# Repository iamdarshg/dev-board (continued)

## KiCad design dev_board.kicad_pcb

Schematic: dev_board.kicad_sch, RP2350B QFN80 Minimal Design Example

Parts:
C3: 15p; C_0402_1005Metric; not fitted
C4: 15p; C_0402_1005Metric
C6, C7: 4.7u; C_0402_1005Metric_small_pads
C8, C11, C12, C13, C14, C15, C16, C17, C18, C20, C21, C22, C23, C24, C26, C27, C33, C38, C41, C42, C43, C44, C45, C49, C50, C51, C52, C54, C55, C56, C57, C59, C61, C63, C66, C67, C75, C77, C82, C85, C86, C87, C88, C90, C92, C93, C94: 100n; C_0402_1005Metric
C9, C10: 4.7u; C_0402_1005Metric
C19: 10u; C_0805_2012Metric
C25, C28, C30, C31, C34, C35, C46, C53, C58, C62, C68, C70, C72, C74, C76, C83, C84: 10u; C_0402_1005Metric
C29, C32, C36, C37, C60: 1u; C_0402_1005Metric
C39, C40, C81: 10n; C_0402_1005Metric
C47, C48, C69, C71, C73, C78, C79, C80: 2.2u; C_0402_1005Metric
C89: 1n; C_0402_1005Metric
C91: 22p; C_0402_1005Metric
C95: 47n; C_0402_1005Metric
C96, C97, C98: 100p; C_0402_1005Metric
FL1: 0900PC15A0036; Rohm_MLGA010V020A_LGA-10_2x2mm_P0.45mm_LayoutBorder2x3y
IC1: AD9609BCPZRL7-80; QFN50P500X500X100-33N; Manufacturer_Part_Number AD9609BCPZRL7-80; Mouser Part Number 584-AD9609BCPZR7-80
IC2: ENS161-BLGT_LGA9_T&R_1k5; ENS161BLGTLGA9TR1k5; Manufacturer_Part_Number ENS161-BLGT LGA9 T&R 1k5; Mouser Part Number 135-ENS161BGLTT&R1K5
IC3: ICM-42670-P; ICM42670P; Manufacturer_Part_Number ICM-42670-P; Mouser Part Number 410-ICM-42670-P
IC4: IWRL6432BDBAAMFR; BGA102C50P12X12_645X645X97; Manufacturer_Part_Number IWRL6432BDBAAMFR
IC5, IC10: MP4541GN-Z; SOIC127P600X170-9N; Manufacturer_Part_Number MP4541GN-Z; Mouser Part Number 946-MP4541GN-Z
IC6: THS8136IPHPR; QFP50P900X900X120-49N; Manufacturer_Part_Number THS8136IPHPR; Mouser Part Number 595-THS8136IPHPR
IC7, IC9: TPS40304ADRCR; Manufacturer_Part_Number TPS40304ADRCR; Mouser Part Number 595-TPS40304ADRCR
IC8: XCC1352R1F3RGZR; QFN50P700X700X100-49N-D; Manufacturer_Part_Number XCC1352R1F3RGZR
J2: Conn_02x26_Odd_Even; PinHeader_2x26_P2.54mm_Vertical
J4: SM03B-SRSS-TB; JST_SH_SM03B-SRSS-TB_1x03-1MP_P1.00mm_Horizontal
J5: STM32H7 GPIO/Fabric Breakout A; PinHeader_2x26_P2.54mm_Vertical
J6: STM32H7 GPIO/Fabric Breakout B; PinHeader_2x26_P2.54mm_Vertical
J9: HS/IWRL Fabric Breakout; PinHeader_2x26_P2.54mm_Vertical
J10: RJ45 / 8P8C LED; RJ45_Amphenol_RJMG1BD3B8K1ANR
J11: SMA_RF_LAUNCH; SMA_Amphenol_132134-10_Vertical
J12: RP2350 USB PROGRAM; USB_Micro-B_Amphenol_10103594-0001LF_Horizontal
J13, J14: DNP / not used; USB_Micro-B_Amphenol_10103594-0001LF_Horizontal
J15: IWRL USB PROGRAM; USB_Micro-B_Amphenol_10103594-0001LF_Horizontal
L1: 3.3u; L_pol_2016
L2: 10uH; L_0805_2012Metric
L3: 4.7uH; L_0805_2012Metric
MK1: IM69D120; Infineon_PG-LLGA-5-1
R2, R4, R6, R45, R46, R47, R48: 1k; R_0402_1005Metric
R3, R49, R50: 33; R_0402_1005Metric
R7, R8: 27; R_0402_1005Metric
R9, R10: 4.7k; R_0402_1005Metric
R11, R12, R13, R17, R18, R19, R22, R23, R26, R27, R28, R29: 10k; R_0402_1005Metric
R14: 330k; R_0402_1005Metric
R15, R16: 100k; R_0402_1005Metric
R24: 12.1k; R_0402_1005Metric
R25, R39, R40, R41: 2.2k; R_0402_1005Metric
R30: 0R; R_0402_1005Metric
R31: 3.8k; R_0402_1005Metric
R32, R33, R34, R42, R43, R44: 75; R_0402_1005Metric
R35, R36, R37, R38: 49.9; R_0402_1005Metric
SW1, SW2: SW_Push; SW_Push_1P1T_NO_Vertical_Wuerth_434133025816
TP1, TP2, TP3, TP4, TP5: TestPoint; TestPoint_Pad_3.0x3.0mm
U1: RP2350_80QFN; RP2350-QFN-80-1EP_10x10_P0.4mm_EP3.4x3.4mm_ThermalVias
U2: LPS22HH; ST_HLGA-10_2x2mm_P0.5mm_LayoutBorder3x2y
U3: STM32H750VBTx; LQFP-100_14x14mm_P0.5mm
U4: LAN8742A; VQFN-24-1EP_4x4mm_P0.5mm_EP2.5x2.5mm_ThermalVias
U5: PGA113; TSSOP-10_3x3mm_P0.5mm
U6: MCP6D11T-E/MS; MCP6D11T-E_MSOP-8_3x3mm_P0.65mm
U7: FT232RNL-TUBE; SSOP-28_5.3x10.2mm_P0.65mm
U8: XMSSJJ3G0PA-054; SOT-363_SC-70-6
Y1: ABM8-272-T3; Crystal_SMD_3225-4Pin_3.2x2.5mm
Y2: XRCMD48M000F1P2AR0; Crystal_SMD_2016-4Pin_2.0x1.6mm

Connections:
+3V3: C6.1, C12.1, C13.1, C14.1, C15.1, C16.1, C17.1, C18.1, C19.1, C20.1, C21.1, C22.1, C23.1, C24.1, C25.1, C26.1, C27.1, C28.1, C34.1, C35.1, C41.1, C42.1, C43.1, C44.1, C45.1, C46.1, C50.1, C51.1, C52.1, C62.1, C63.1, C80.1, C81.1, C82.1, C83.1, C84.1, C85.1, C86.1, C88.2, FL1.1 (ANT_2G4), IC2.4 (VDD), IC2.5 (VDDIO), IC3.5 (VDDIO), IC3.7 (FSYNC), IC3.8 (VDD), IC3.12 (AP_CS), IC6.40 (AVDD_2), IC6.44 (AVDD), IC8.13 (VDDS2), IC8.22 (VDDS3), IC8.34 (VDDS_DCDC), IC8.44 (VDDS), J2.2, J9.18, J9.40, J9.44, J9.52, L2.1, L3.2, MK1.5 (GND), R3.1, R9.1, R10.1, R13.1, R14.1, R17.2, R23.2, R25.2, R26.2, R28.2, R39.2, R40.2, R41.2, U1.5 (IOVDD), U1.15 (IOVDD), U1.24 (IOVDD), U1.29 (IOVDD), U1.41 (IOVDD), U1.50 (IOVDD), U1.59 (ADC_AVDD), U1.60 (IOVDD), U1.64 (VREG_VIN), U1.68 (USB_OTP_VDD), U1.69 (QSPI_IOVDD), U1.76 (IOVDD), U2.1 (Vdd_IO), U2.6 (~CS), U2.10 (VDD), U3.6 (VBAT), U3.11 (VDD), U3.20 (VREF+), U3.21 (VDDA), U3.27 (VDD), U3.50 (VDD), U3.75 (VDD), U3.100 (VDD), U4.1 (VDD2A), U4.9 (VDDIO), U4.19 (VDD1A), U5.1 (AV_{DD}), U5.10 (DV_{DD}), U6.3 (VDD), U8.3 (PORT2), U8.4 (VDD)
/ADC_AVDD_1V8: C55.1, C56.1, C57.1, C58.1, IC1.3 (AVDD_2), IC1.24 (AVDD_4), IC1.29 (AVDD_3), IC1.32 (AVDD)
/ADC_CLK_N: IC1.2 (CLK-), J5.18, U3.45 (PE15)
/ADC_CLK_P: IC1.1 (CLK+), J5.17, U3.44 (PE14)
/ADC_CSB: IC1.4 (CSB), J5.14, U3.41 (PE11)
/ADC_D0: IC1.11 ((LSB)D0), J5.3, U3.97 (PE0)
/ADC_D1: IC1.12 (D1), J5.4, U3.98 (PE1)
/ADC_D2: IC1.14 (D2), J5.5, U3.1 (PE2)
/ADC_D3: IC1.15 (D3), J5.6, U3.2 (PE3)
/ADC_D4: IC1.16 (D4), J5.7, U3.3 (PE4)
/ADC_D5: IC1.17 (D5), J5.8, U3.4 (PE5)
/ADC_D6: IC1.18 (D6), J5.9, U3.5 (PE6)
/ADC_D7: IC1.19 (D7), J5.10, U3.37 (PE7)
/ADC_D8: IC1.20 (D8), J5.11, U3.38 (PE8)
/ADC_D9: IC1.21 (D9(MSB)), J5.12, U3.39 (PE9)
/ADC_DCO: IC1.22 (DCO), J5.13, U3.40 (PE10)
/ADC_DRVDD: C59.1, IC1.13 (DRVD0)
/ADC_MODE_OR: IC1.23 (MODE/OR)
/ADC_RBIAS: IC1.28 (RBIAS), R29.1
/ADC_SCLK: IC1.5 (SCLK/DFS), J5.15, U3.42 (PE12)
/ADC_SDIO: IC1.6 (SDIO/PDWN), J5.16, U3.43 (PE13)
/ADC_SENSE: IC1.26 (SENSE), R30.1
/ADC_VCM: C61.1, IC1.27 (VCM), R46.1, U5.4 (V_{REF}), U6.2 (VOCM)
/ADC_VIN_N: C91.2, IC1.30 (VIN-), R49.2
/ADC_VIN_P: C91.1, IC1.31 (VIN+), R50.2
/ADC_VREF: C60.1, IC1.25 (VREF), R30.2
/CC_DCDC_SW: IC8.33 (DCDC_SW), L2.2
/CC_DCOUPL: C29.1, IC8.23 (DCOUPL)
/CC_DIO_3: IC8.8 (DIO_3), J6.31
/CC_DIO_4: IC8.9 (DIO_4), J6.32
/CC_DIO_5: IC8.10 (DIO_5), J6.33
/CC_DIO_7: IC3.9 (INT2), IC8.12 (DIO_7), J2.39, J6.35, U1.36 (GPIO28)
/CC_DIO_8: IC8.14 (DIO_8), J2.37, J6.36, U1.37 (GPIO29)
/CC_DIO_9: IC8.15 (DIO_9), J2.35, J6.37, U1.38 (GPIO30)
/CC_DIO_10: IC8.16 (DIO_10), J2.33, J6.38, U1.39 (GPIO31)
/CC_DIO_11: IC8.17 (DIO_11), J6.39
/CC_DIO_12: IC8.18 (DIO_12), J6.40
/CC_DIO_13: IC8.19 (DIO_13), J6.41
/CC_DIO_14: IC8.20 (DIO_14), J6.42
/CC_DIO_15: IC8.21 (DIO_15), J6.43
/CC_DIO_16: IC8.26 (DIO_16), J6.44
/CC_DIO_17: IC8.27 (DIO_17), J9.39
/CC_DIO_18: IC8.28 (DIO_18), J6.46
/CC_DIO_19: IC8.29 (DIO_19), J9.41
/CC_DIO_20: IC8.30 (DIO_20), J6.48
/CC_DIO_21: IC8.31 (DIO_21), J9.43
/CC_DIO_22: IC8.32 (DIO_22), J6.50
/CC_DIO_23: IC8.36 (DIO_23), J9.45
/CC_DIO_24: IC8.37 (DIO_24), J6.52
/CC_DIO_25: IC8.38 (DIO_25), J9.47
/CC_DIO_26: IC8.39 (DIO_26), J6.51
/CC_DIO_27: IC8.40 (DIO_27), J9.49
/CC_DIO_28: IC8.41 (DIO_28), J6.49
/CC_DIO_29: IC8.42 (DIO_29), J9.51
/CC_DIO_30: C97.2, FL1.4 (ANT_SUBG), IC8.43 (DIO_30), J6.47, U8.6 (CTL)
/CC_PROG_USB_D+: J14.3 (D+)
/CC_PROG_USB_D-: J14.2 (D-)
/CC_PROG_USB_VBUS: J14.4 (ID)
/CC_RESET_N: IC8.35 (RESET_N), J9.46, R13.2
/CC_RF_N_2G4: FL1.8 (RF_N_2G4), IC8.2 (RF_N_2_4GHZ)
/CC_RF_N_SUBG: FL1.6 (RF_N_SUBG), IC8.4 (RF_N_SUB_1GHZ)
/CC_RF_P_2G4: C98.2, FL1.9 (RF_P_2G4), IC8.1 (RF_P_2_4GHZ)
/CC_RF_P_SUBG: FL1.7 (RF_P_SUBG), IC8.3 (RF_P_SUB_1GHZ)
/CC_TCKC: IC8.25 (JTAG_TCKC), J6.45
/CC_TMSC: IC8.24 (JTAG_TMSC), J9.50
/CC_VDDR: C30.1, IC8.45 (VDDR), IC8.48 (VDDR_RF)
/CC_X32K_Q1: IC8.6 (X32K_Q1)
/CC_X32K_Q2: IC8.7 (X32K_Q2)
/CC_X48M_N: IC8.46 (X48M_N), Y2.3
/CC_X48M_P: IC8.47 (X48M_P), Y2.1
/DAC_B0: IC6.10 (B0), J5.19, U3.81 (PD0)
/DAC_B1: IC6.9 (B1), J5.20, U3.82 (PD1)
/DAC_B2: IC6.8 (B2), J5.21, U3.83 (PD2)
/DAC_B3: IC6.7 (B3), J5.22, U3.84 (PD3)
/DAC_B4: IC6.6 (B4), J5.23, U3.85 (PD4)
/DAC_B5: IC6.5 (B5), J5.24, U3.86 (PD5)
/DAC_B6: IC6.4 (B6), J5.25, U3.87 (PD6)
/DAC_B7: IC6.3 (B7), J5.26, U3.88 (PD7)
/DAC_B8: IC6.2 (B8), J5.27, U3.55 (PD8)
/DAC_B9: IC6.1 (B9), J5.28, U3.56 (PD9)
/DAC_BLANK_N: IC6.23 (~BLANK), J6.24, R40.1, U3.66 (PC9)
/DAC_CLK: IC6.26 (CLK), J6.21, R39.1, U3.63 (PC6)
/DAC_COMP: C66.1, IC6.39 (COMP)
/DAC_FSADJ: IC6.38 (FSADJ), R31.1
/DAC_G0: IC6.36 (G0), J5.29, U3.57 (PD10)
/DAC_G1: IC6.35 (G1), J5.30, U3.58 (PD11)
/DAC_G2: IC6.34 (G2), J5.31, U3.59 (PD12)
/DAC_G3: IC6.33 (G3), J5.32, U3.60 (PD13)
/DAC_G4: IC6.32 (G4), J5.33, U3.61 (PD14)
/DAC_G5: IC6.31 (G5), J5.34, U3.62 (PD15)
/DAC_G6: IC6.30 (G6), J5.51, U3.34 (PB0)
/DAC_G7: IC6.29 (G7), J5.52, U3.35 (PB1)
/DAC_G8: IC6.28 (G8), J6.1, U3.36 (PB2)
/DAC_G9: IC6.27 (G9), J6.2, U3.89 (PB3)
/DAC_M1: IC6.47 (M1), J6.25, U3.78 (PC10)
/DAC_M2: IC6.48 (M2), J6.26, U3.79 (PC11)
/DAC_R0: IC6.13 (R0), J6.3, U3.90 (PB4)
/DAC_R1: IC6.14 (R1), J6.4, U3.91 (PB5)
/DAC_R2: IC6.15 (R2), J6.7, U3.95 (PB8)
/DAC_R3: IC6.16 (R3), J6.8, U3.96 (PB9)
/DAC_R4: IC6.17 (R4), J5.2, U3.13 (PH1)
/DAC_R5: IC6.18 (R5), J6.13, U3.53 (PB14)
/DAC_R6: IC6.19 (R6), J6.14, U3.54 (PB15)
/DAC_R7: IC6.20 (R7), J6.15, U3.15 (PC0)
/DAC_R8: IC6.21 (R8), J6.17, U3.17 (PC2_C)
/DAC_R9: IC6.22 (R9), J6.10, U3.47 (PB11)
/DAC_SYNC_N: IC6.24 (~SYNC), J6.23, R41.1, U3.65 (PC8)
/DAC_SYNC_T: IC6.25 (SYNC-T), J6.22, U3.64 (PC7)
/DAC_VREF: C67.1, IC6.37 (VREF)
/ENS_ADDR: IC2.3 (MISO_/_ADDR), R11.1
/ETH_CRS_DV: J5.42, U3.31 (PA7), U4.11 (CRS_DV/MODE2)
/ETH_CT: C87.1, R35.2, R36.2, R37.2, R38.2
/ETH_CT1: J10.5 (CT2)
/ETH_CT2: J10.4 (CT1)
/ETH_MDC: J6.16, U3.16 (PC1), U4.13 (MDC)
/ETH_MDIO: J5.37, R25.1, U3.24 (PA2), U4.12 (MDIO)
/ETH_REFCLK_INT: J5.36, U3.23 (PA1), U4.14 (~INT/REFCLKO)
/ETH_RST_N: R26.1, U4.15 (~RST)
/ETH_RXD0: J6.19, U3.32 (PC4), U4.8 (RXD0/MODE0)
/ETH_RXD1: J6.20, U3.33 (PC5), U4.7 (RXD1/MODE1)
/ETH_RXER: U4.10 (RXER/PHYAD0)
/ETH_RX_N: J10.6 (RD-), R38.1, U4.22 (RXN)
/ETH_RX_P: J10.3 (RD+), R37.1, U4.23 (RXP)
/ETH_TXD0: J6.11, U3.51 (PB12), U4.17 (TXD0)
/ETH_TXD1: J6.12, U3.52 (PB13), U4.18 (TXD1)
/ETH_TXEN: J6.9, U3.46 (PB10), U4.16 (TXEN)
/ETH_TX_N: J10.2 (TD-), R36.1, U4.20 (TXN)
/ETH_TX_P: J10.1 (TD+), R35.1, U4.21 (TXP)
/GPIO0: J2.4, U1.77 (GPIO0)
/GPIO1: J2.6, U1.78 (GPIO1)
/GPIO2: J2.8, MK1.3 (CLOCK), U1.79 (GPIO2)
/GPIO3: J2.10, MK1.4 (SELECT), U1.80 (GPIO3)
/GPIO4: J2.12, MK1.1 (DATA), U1.1 (GPIO4)
/GPIO5: J2.14, U1.2 (GPIO5)
/GPIO7: IC3.4 (INT1_/_INT), J2.18, U1.4 (GPIO7)
/GPIO8: J2.20, U1.6 (GPIO8)
/GPIO9: J2.22, U1.7 (GPIO9), U2.7 (INT_DRDY)
/GPIO10: J2.24, U1.8 (GPIO10), U5.7 (SCLK)
/GPIO11: J2.26, U1.9 (GPIO11), U5.8 (DIO)
/GPIO12: J2.28, U1.11 (GPIO12), U5.9 (~CS)
/GPIO13: J2.30, U1.12 (GPIO13), U6.7 (~PD)
/GPIO14: J2.32, U1.13 (GPIO14)
/GPIO15: J2.34, U1.14 (GPIO15)
/GPIO16: J2.36, J5.35, J9.1, U1.16 (GPIO16), U3.22 (PA0)
/GPIO17: J2.38, J5.38, J9.2, U1.17 (GPIO17), U3.25 (PA3)
/GPIO18: J2.40, J5.39, J9.3, U1.18 (GPIO18), U3.28 (PA4)
/GPIO19: J2.42, J5.40, J9.4, U1.19 (GPIO19), U3.29 (PA5)
/GPIO20: J2.44, J5.41, J9.5, U1.20 (GPIO20), U3.30 (PA6)
/GPIO21: J2.46, J5.43, J9.6, U1.21 (GPIO21), U3.67 (PA8)
/GPIO22: J2.48, J5.44, J9.7, U1.22 (GPIO22), U3.68 (PA9)
/GPIO23: J2.50, J5.45, J9.8, U1.23 (GPIO23), U3.69 (PA10)
/GPIO24: J2.52, J5.46, J9.9, U1.25 (GPIO24), U3.70 (PA11)
/GPIO25: J2.51, J5.47, J9.10, U1.26 (GPIO25), U3.71 (PA12)
/GPIO26: J2.49, U1.27 (GPIO26)
/GPIO32: IC4.A10 (QSPI_CS), J2.31, J5.50, J9.11, U1.40 (GPIO32), U3.77 (PA15)
/GPIO33: IC4.A11 (QSPI_CLK), J2.29, J6.27, J9.12, U1.42 (GPIO33), U3.80 (PC12)
/GPIO34: IC4.B11 (QSPI[0]), J2.27, J6.28, J9.13, U1.43 (GPIO34), U3.7 (PC13)
/GPIO35: IC4.B8 (QSPI[1]), J2.25, J6.29, J9.14, U1.44 (GPIO35), U3.8 (PC14)
/GPIO36: IC4.B10 (QSPI[2]), J2.23, J6.30, J9.15, U1.45 (GPIO36), U3.9 (PC15)
/GPIO37: IC4.B9 (QSPI[3]), J2.21, J5.1, J9.16, U1.46 (GPIO37)
/GPIO38: J2.19, U1.47 (GPIO38)
/GPIO39: J2.17, U1.48 (GPIO39)
/GPIO40_ADC0: J2.15, U1.49 (GPIO40_ADC0)
/GPIO41_ADC1: J2.13, U1.52 (GPIO41_ADC1)
/GPIO42_ADC2: J2.11, U1.53 (GPIO42_ADC2)
/GPIO43_ADC3: J2.9, U1.54 (GPIO43_ADC3)
/GPIO44_ADC4: J2.7, U1.55 (GPIO44_ADC4)
/GPIO45_ADC5: J2.5, U1.56 (GPIO45_ADC5)
/GPIO46_ADC6: J2.3, U1.57 (GPIO46_ADC6)
/GPIO47_ADC7: J2.1, U1.58 (GPIO47_ADC7)
/IMU_AD0: IC3.1 (AP_SDO_/_AP_AD0)
/IWR_CLKM: IC4.B1 (CLKM)
/IWR_CLKP: IC4.D1 (CLKP)
/IWR_FTDI_3V3OUT: C94.1, U7.17 (3V3OUT)
/IWR_GPADC1: IC4.M6 (GPADC1), J9.36
/IWR_GPADC2: IC4.L6 (GPADC2), J9.37
/IWR_GPIO_2: IC4.H10 (GPIO_2), J9.32
/IWR_GPIO_5: IC4.J10 (GPIO_5), J9.33
/IWR_HOST_CLK_REQ: IC4.M10 (HOST_CLK__REQ), J9.34
/IWR_NERROR: IC4.K11 (NERROR__OUT), J9.31
/IWR_NRST: IC4.L10 (NRESET), J9.26
/IWR_OSC_CLK_OUT: IC4.A7 (OSC_CLK__OUT)
/IWR_PMIC_CLKOUT: IC4.H11 (PMIC__CLKOUT), J9.35
/IWR_PROG_USB_D+: J15.3 (D+), U7.15 (USBD+)
/IWR_PROG_USB_D-: J15.2 (D-), U7.16 (USBD-)
/IWR_RX1: IC4.K1 (RX1)
/IWR_RX2: IC4.H1 (RX2)
/IWR_RX3: IC4.F1 (RX3)
/IWR_SPI_CLK: IC4.D10 (SPIA_CLK), J9.21
/IWR_SPI_CS_N: IC4.D11 (SPIA_CS0__N), J9.22
/IWR_SPI_MISO: IC4.C11 (SPIA_MISO), J9.20
/IWR_SPI_MOSI: IC4.B12 (SPIA_MOSI), J9.19
/IWR_TCK: IC4.C12 (TCK), J9.27
/IWR_TDI: IC4.G11 (TDI), J9.29
/IWR_TDO: IC4.E11 (TDO), J9.30
/IWR_TMS: IC4.E12 (TMS), J9.28
/IWR_TX1: IC4.A3 (TX1)
/IWR_TX2: IC4.A5 (TX2)
/IWR_UART_RTS: IC4.L11 (UARTA_RTS), J9.25
/IWR_UART_RX: IC4.J11 (UARTA_RX), J9.24, U7.1 (TXD)
/IWR_UART_TX: IC4.L12 (UARTA_TX), J9.23, U7.5 (RXD)
/IWR_USB_VBUS: C92.1, J15.1 (VBUS), U7.20 (VCC)
/IWR_VDDA_1V0RF: C72.1, C73.1, IC4.L3 (VDDA_10RF_1), IC4.M3 (VDDA_10RF_2)
/IWR_VDDA_1V2RF: C68.1, C69.1, IC4.L4 (VDDA_12RF_1), IC4.M4 (VDDA_12RF_2)
/IWR_VDDA_1V8: C76.1, C77.1, IC4.F3 (VDDA__18VCO), IC4.J5 (VIN_18PM), IC4.L5 (VDDA_18BB_1), IC4.M5 (VDDA_18BB_2)
/IWR_VDD_1V2: IC4.C9 (VDD_1), IC4.G7 (VDD_2), IC4.G8 (VDD_3), IC4.G9 (VDD_4), IC4.H8 (VDD_5), IC4.K7 (VDD_6)
/IWR_VDD_SRAM: C70.1, C71.1, IC4.M7 (VDD_SRAM)
/IWR_VIO_1V8: C74.1, C75.1, C93.1, IC4.C6 (VIOIN__18CLK), IC4.C8 (VIOIN_18_1), IC4.G12 (VIOIN_1), IC4.K12 (VIOIN_18_2), IC4.L8 (VIOIN_18_3), IC4.M8 (VIOIN_18_4), IC4.M11 (VIOIN_2), U7.4 (VCCIO), U7.19 (~RESET)
/IWR_VOUT_1V4_APLL: C79.1, IC4.G5 (VOUT__14APLL)
/IWR_VOUT_1V4_SYNTH: C78.1, IC4.D3 (VOUT__14SYNTH)
/IWR_VPP: IC4.A8 (VPP)
/LPS_SA0: R12.1, U2.5 (SA0)
/MP_BST: C33.1, IC5.5 (BST), IC10.5 (BST)
/MP_EN: IC5.1 (EN), IC10.1 (EN), R16.2
/MP_FB: IC5.4 (FB), IC10.4 (FB), R14.2, R15.1
/MP_FREQ: IC5.3 (FREQ), IC10.3 (FREQ)
/MP_SW: C33.2, IC5.6 (SW), IC10.6 (SW), L3.1
/MP_VCC: C32.1, IC5.2 (VCC), IC10.2 (VCC)
/PHY_LED1_REGOFF: J10.9 (LED1A), R27.1, U4.3 (LED1/REGOFF)
/PHY_LED2_INTSEL: J10.11 (LED2A), R28.1, U4.2 (LED2/~INTSEL)
/PHY_RBIAS: R24.1, U4.24 (RBIAS)
/PHY_VDDCR: C53.1, C54.1, U4.6 (VDDCR)
/PHY_XTAL1: U4.5 (XTAL1/CLKIN)
/PHY_XTAL2: U4.4 (XTAL2)
/QSPI_SCLK: U1.71 (QSPI_SCLK)
/QSPI_SD0: U1.72 (QSPI_SD0)
/QSPI_SD1: U1.74 (QSPI_SD1)
/QSPI_SD2: U1.73 (QSPI_SD2)
/QSPI_SD3: U1.70 (QSPI_SD3)
/QSPI_SS: R6.1, U1.75 (QSPI_SS)
/RUN: J2.41, SW2.2, U1.35 (RUN)
/SCOPE_AUX_IN: TP2.1, U5.2 (CH1)
/SCOPE_IN: TP1.1, U5.3 (CH0/V_{CAL})
/SENS_I2C_SCL: IC2.2 (SCLK_/_SCL), IC3.13 (AP_SCL_/_AP_SCLK), J6.5, R9.2, U2.2 (SCL), U3.92 (PB6)
/SENS_I2C_SDA: IC2.1 (MOSI_/_SDA), IC3.14 (AP_SDA_/_AP_SDIO_/_AP_SDI), J6.6, R10.2, U2.4 (SDA), U3.93 (PB7)
/STM_NRST: C49.1, R23.1, U3.14 (NRST)
/STM_PC3_C: J6.18, U3.18 (PC3_C)
/STM_SWCLK: J5.49, U3.76 (PA14)
/STM_SWDIO: J5.48, U3.72 (PA13)
/STM_USB_FS_DM: J13.2 (D-)
/STM_USB_FS_DP: J13.3 (D+)
/STM_USB_VBUS: J13.1 (VBUS)
/STM_VCAP1: C47.1, U3.48 (VCAP)
/STM_VCAP2: C48.1, U3.73 (VCAP)
/STM_VCAP_A: U3.12 (PH0)
/TPS_BOOT: C38.1, IC7.6 (BOOT), IC9.6 (BOOT)
/TPS_BP: C37.1, IC7.10 (BP), IC9.10 (BP)
/TPS_COMP: C40.1, IC7.4 (COMP), IC9.4 (COMP), R22.1
/TPS_ENSS: C39.1, IC7.2 (EN/SS), IC9.2 (EN/SS)
/TPS_FB: IC7.5 (FB), IC9.5 (FB), R18.2, R19.1, R22.2
/TPS_HDRV: IC7.7 (HDRV), IC9.7 (HDRV)
/TPS_LDRV_OC: IC7.9 (LDRV/_OC), IC9.9 (LDRV/_OC)
/TPS_PGOOD: IC7.3 (PGOOD), IC9.3 (PGOOD), R17.1
/TPS_SW: C38.2, IC7.8 (SW), IC9.8 (SW)
/USB_D+: J12.3 (D+), R7.1
/USB_D-: J12.2 (D-), R8.1
/VGA_B: IC6.45 (AB), R34.1, R44.1, TP4.1
/VGA_G: IC6.41 (AG), R33.1, R43.1, TP5.1
/VGA_MON: R42.2, R43.2, R44.2
/VGA_R: IC6.43 (AR), R32.1, R42.1, TP3.1
/VIN_RAW: C31.1, C36.1, IC5.8 (VIN), IC7.1 (VDD), IC9.1 (VDD), IC10.8 (VIN), J12.1 (VBUS), J14.1 (VBUS), R16.1
/VREG_AVDD: C9.1, R3.2, U1.61 (VREG_AVDD)
/VREG_FB: U1.34 (SWD)
/XIN: C3.1, U1.30 (XIN), Y1.1
/XOUT: R2.1, U1.31 (XOUT)
/~USB_BOOT: R6.2, SW1.2
GND: C3.2, C4.2, C6.2, C7.2, C8.2, C9.2, C10.2, C11.2, C12.2, C13.2, C14.2, C15.2, C16.2, C17.2, C18.2, C19.2, C20.2, C21.2, C22.2, C23.2, C24.2, C25.2, C26.2, C27.2, C28.2, C29.2, C30.2, C31.2, C32.2, C34.2, C35.2, C36.2, C37.2, C39.2, C40.2, C41.2, C42.2, C43.2, C44.2, C45.2, C46.2, C47.2, C48.2, C49.2, C50.2, C51.2, C52.2, C53.2, C54.2, C55.2, C56.2, C57.2, C58.2, C59.2, C60.2, C61.2, C62.2, C63.2, C66.2, C67.2, C68.2, C69.2, C70.2, C71.2, C72.2, C73.2, C74.2, C75.2, C76.2, C77.2, C78.2, C79.2, C80.2, C81.2, C82.2, C83.2, C84.2, C85.2, C86.2, C87.2, C88.1, C89.1, C90.1, C92.2, C93.2, C94.2, C98.1, FL1.2 (GND), FL1.3 (GND), FL1.10 (GND), IC1.33 (EPAD), IC2.8 (VSS_1), IC2.9 (VSS_2), IC3.6 (GND), IC4.A1 (VSSA_1), IC4.A2 (VSSA_2), IC4.A4 (VSSA_3), IC4.A6 (VSSA_4), IC4.B2 (VSSA_5), IC4.B3 (VSSA_6), IC4.B4 (VSSA_7), IC4.B5 (VSSA_8), IC4.B6 (VSSA_9), IC4.B7 (VSS_2), IC4.C1 (VSSA_10), IC4.C2 (VSSA_11), IC4.D2 (VSSA_12), IC4.E1 (VSSA_13), IC4.E2 (VSSA_14), IC4.E5 (VSSA_PM), IC4.E6 (VSS_3), IC4.E7 (VSS_4), IC4.E8 (VSS_5), IC4.E9 (VSS_6), IC4.F2 (VSSA_15), IC4.F5 (VSSA_16), IC4.F6 (VSS_7), IC4.F7 (VSS_8), IC4.F8 (VSS_9), IC4.F9 (VSS_10), IC4.G1 (VSSA_17), IC4.G2 (VSSA_18), IC4.H2 (VSSA_19), IC4.H12 (VSS_11), IC4.J1 (VSSA_20), IC4.J2 (VSSA_21), IC4.K2 (VSSA_22), IC4.K9 (VSS_12), IC4.L1 (VSSA_23), IC4.L2 (VSSA_24), IC4.M1 (VSSA_25), IC4.M2 (VSSA_26), IC4.M12 (VSS_13), IC5.7 (GND), IC5.9 (EP), IC6.11 (DVSS), IC6.12 (DVDD), IC6.42 (AVSS_2), IC6.46 (AVSS), IC6.49 (EP), IC7.11 (GND_1), IC7.12 (GND_2), IC7.13 (GND_3), IC7.14 (GND_4), IC7.15 (GND_5), IC8.49 (EP), IC9.11 (GND_1), IC9.12 (GND_2), IC9.13 (GND_3), IC9.14 (GND_4), IC9.15 (GND_5), IC10.7 (GND), IC10.9 (EP), J4.2, J4.MP (MountPin), J9.17, J9.38, J9.42, J9.48, J10.13 (Shield), J11.2 (Ext), J12.5 (GND), J12.6 (Shield), J13.5 (GND), J13.6 (Shield), J14.5 (GND), J14.6 (Shield), J15.5 (GND), J15.6 (Shield), MK1.2 (VDD), R4.2, R11.2, R12.2, R15.2, R19.2, R24.2, R27.2, R29.2, R31.2, R32.2, R33.2, R34.2, SW1.1, U1.62 (VREG_PGND), U1.81 (GND), U2.3 (GND), U2.8 (GND), U2.9 (GND), U3.10 (VSS), U3.19 (VSSA), U3.26 (VSS), U3.49 (VSS), U3.74 (VSS), U3.94 (BOOT0), U3.99 (VSS), U4.25 (VSS), U5.6 (GND), U6.6 (VSS), U7.7 (GND), U7.18 (GND), U7.21 (GND), U7.25 (AGND), U7.26 (TEST), U8.2 (GND), Y1.2, Y1.4, Y2.2, Y2.4
unnamed: C4.1, R2.2, Y1.3
unnamed: C96.1, J11.1 (In)
unnamed: C96.2, U8.5 (RFC)
unnamed: C97.1, U8.1 (PORT1)
unnamed: FL1.5 (RX_TX), IC8.5 (RX_TX)
unnamed: R4.1, SW2.1
unnamed: R8.2, U1.66 (USB_DM)
unnamed: R7.2, U1.67 (USB_DP)
unnamed: R45.1, U5.5 (V_{OUT})
unnamed: R45.2, R48.1, U6.8 (IN+)
unnamed: C89.2, R46.2, R47.1, U6.1 (IN-)
unnamed: C90.2, R47.2, R50.1, U6.4 (OUT+)
unnamed: R48.2, R49.1, U6.5 (OUT-)

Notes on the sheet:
DAC island: PD/PB/PC/PH1 assigned to THS8136 RGB bus/timing; fabric is kept off these pins.
CC1352 island: recommended decoupling, DCDC and crystal nets
Schematic completion notes
Review before layout: RF matching, ADC analog front-end, Ethernet magnetics, and regulator loop values are topology-dependent.
USB programming ports: J12 RP2350 native USB; J13 STM32 DFU optional via R52/R53; J14 CC1352 programmer bridge USB input, DNP in this revision; J15 IWRL USB-UART at 1.8V I/O.
RJ45 Ethernet island: cable connector / MagJack-side breakout for LAN8742A pairs and LEDs.
CC1352: DCOUPL/VDDR/DCDC support is shown; RF balun/matching network should follow the selected reference design.
Extra explicit passives from datasheet application/BOM sections
RP2350 scope control: GPIO10=PGA SCLK, GPIO11=PGA SDIO, GPIO12=PGA CS_N, GPIO13=MCP6D11 PD_N
IOs
ADC island: AD9609 AVDD/DRVDD/VREF/VCM/RBIAS support
12MHz Crystal
ADC and THS8136 analog support below boundary
CC1352 island: DCOUPL/VDDR/DCDC/crystal support
Power
Codex generated recommended support components - cross-boundary data uses labels only
No generated data wire crosses the horizontal user boundary; shared signals use local net labels.
ADC island: PE0-PE15 assigned to AD9609 data/control/clock nets
Electrical net names preserve existing RP2350 GPIO labels; role notes map those GPIOs to HS_Dx/QSPI functions.
STM32H750 and LAN8742A support below boundary
Ethernet island: LAN8742A RBIAS, VDDCR, magnetics termination
Keep exact/application-specific values for PHY RBIAS 12.1k, Ethernet 49.9R, video 75R, DAC FSADJ 3.8k.
Intentional crossings: GPIO16-GPIO25 are RP-to-STM parallel fabric; GPIO32-GPIO37 are shared RP/STM/IWR QSPI.
STM32/LAN8742A: RMII nets are label-connected below the boundary; unused STM32 GPIOs are intentionally left for expansion.
RF SMA launch: stuff after selected CC1352 balun/matching network; keep 50 ohm controlled impedance.
Place 1k FDA gain/feedback resistors tight to MCP6D11 pins; place 33R/22p ADC filter tight to AD9609 VIN pins.
Buck regulator recommended bootstrap, feedback, soft-start and compensation parts
Boot/strap pins are tied by labels and pull resistors; change these only with firmware/boot-mode review.
Island plan: PE=ADC, PD/PB/PC/PH1=DAC, PA+PC12-15+PH0=fabric, Ethernet keeps existing PA/PB/PC pins.
J9 combines the fabric and IWRL breakout: GPIO32-37 are the IWRL high-speed QSPI bus; lower pins expose IWRL SPIA/UART/JTAG/control.
DAC island: THS8136 DVDD/AVDD/VREF/FSADJ/output loads
Sensor I2C pulls and local decoupling
JST Debug Connector
IWRL island: LDO-output 10u + 2.2u capacitors
IWRL island: LDO-output and supply decoupling below boundary
Power island: buck bootstrap, comp, feedback, SS and FET gate resistors
Make sure R7 and R8 are close to RP2350
IWRL6432: LDO-output caps follow datasheet typical 10u + 2.2u groups; RF pins still need layout/reference-design matching.
RP-to-STM parallel fabric: GPIO16-23=HS_D0-D7, GPIO24=HS_CLK, GPIO25=HS_FRAME
I2C sensor bus: ENS161, ICM-42670-P, and LPS22HH share SENS_I2C_SCL/SDA with one pullup pair; strap ENS_ADDR, IMU_AD0, and LPS_SA0 intentionally; IC2 INTN -> GPIO27 and IC3 INT2 -> GPIO28.

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
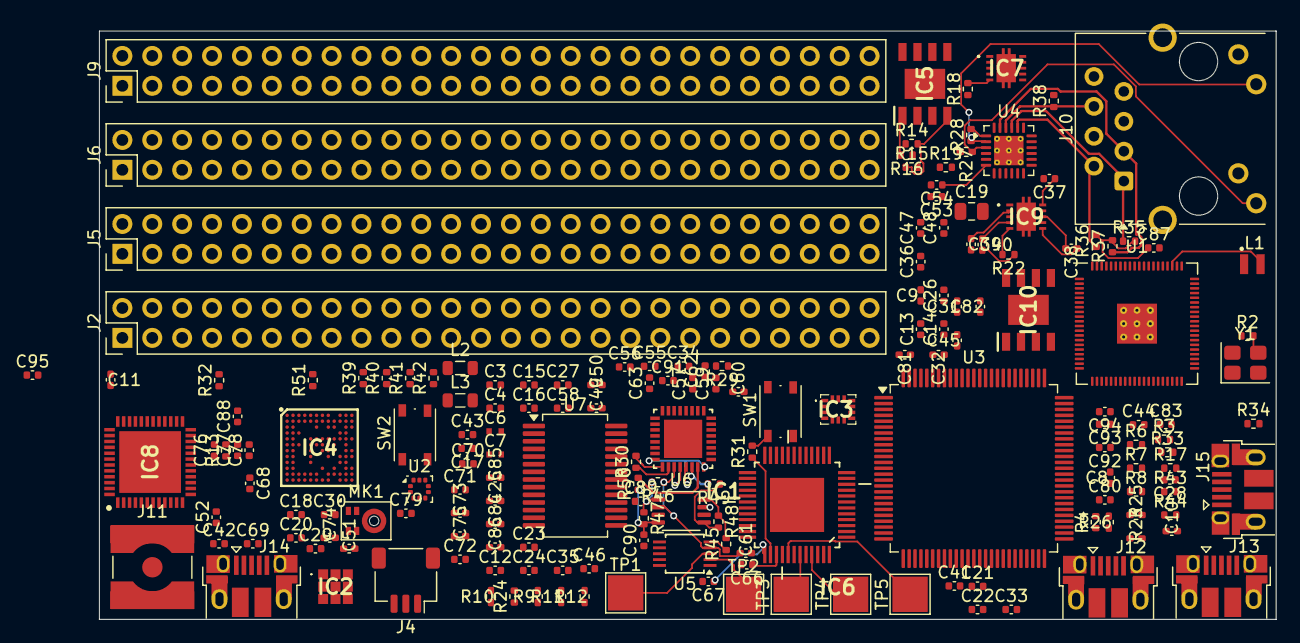
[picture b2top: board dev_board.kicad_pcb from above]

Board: 4 copper layers, 100.0 x 50.0 mm, 177 parts (0 on the bottom side), 243 nets.

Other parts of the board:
R51: 0R/DNP; R_0402_1005Metric

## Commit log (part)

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2026-04-18 demarcation of boundaries, ethenret PHY
2026-05-02 more pcb chanegs, ADC fixes
2026-05-02 more pcb chanegs, placements
2026-05-03 more fixes
2026-05-05 something
2026-05-12 more pcb stuff
